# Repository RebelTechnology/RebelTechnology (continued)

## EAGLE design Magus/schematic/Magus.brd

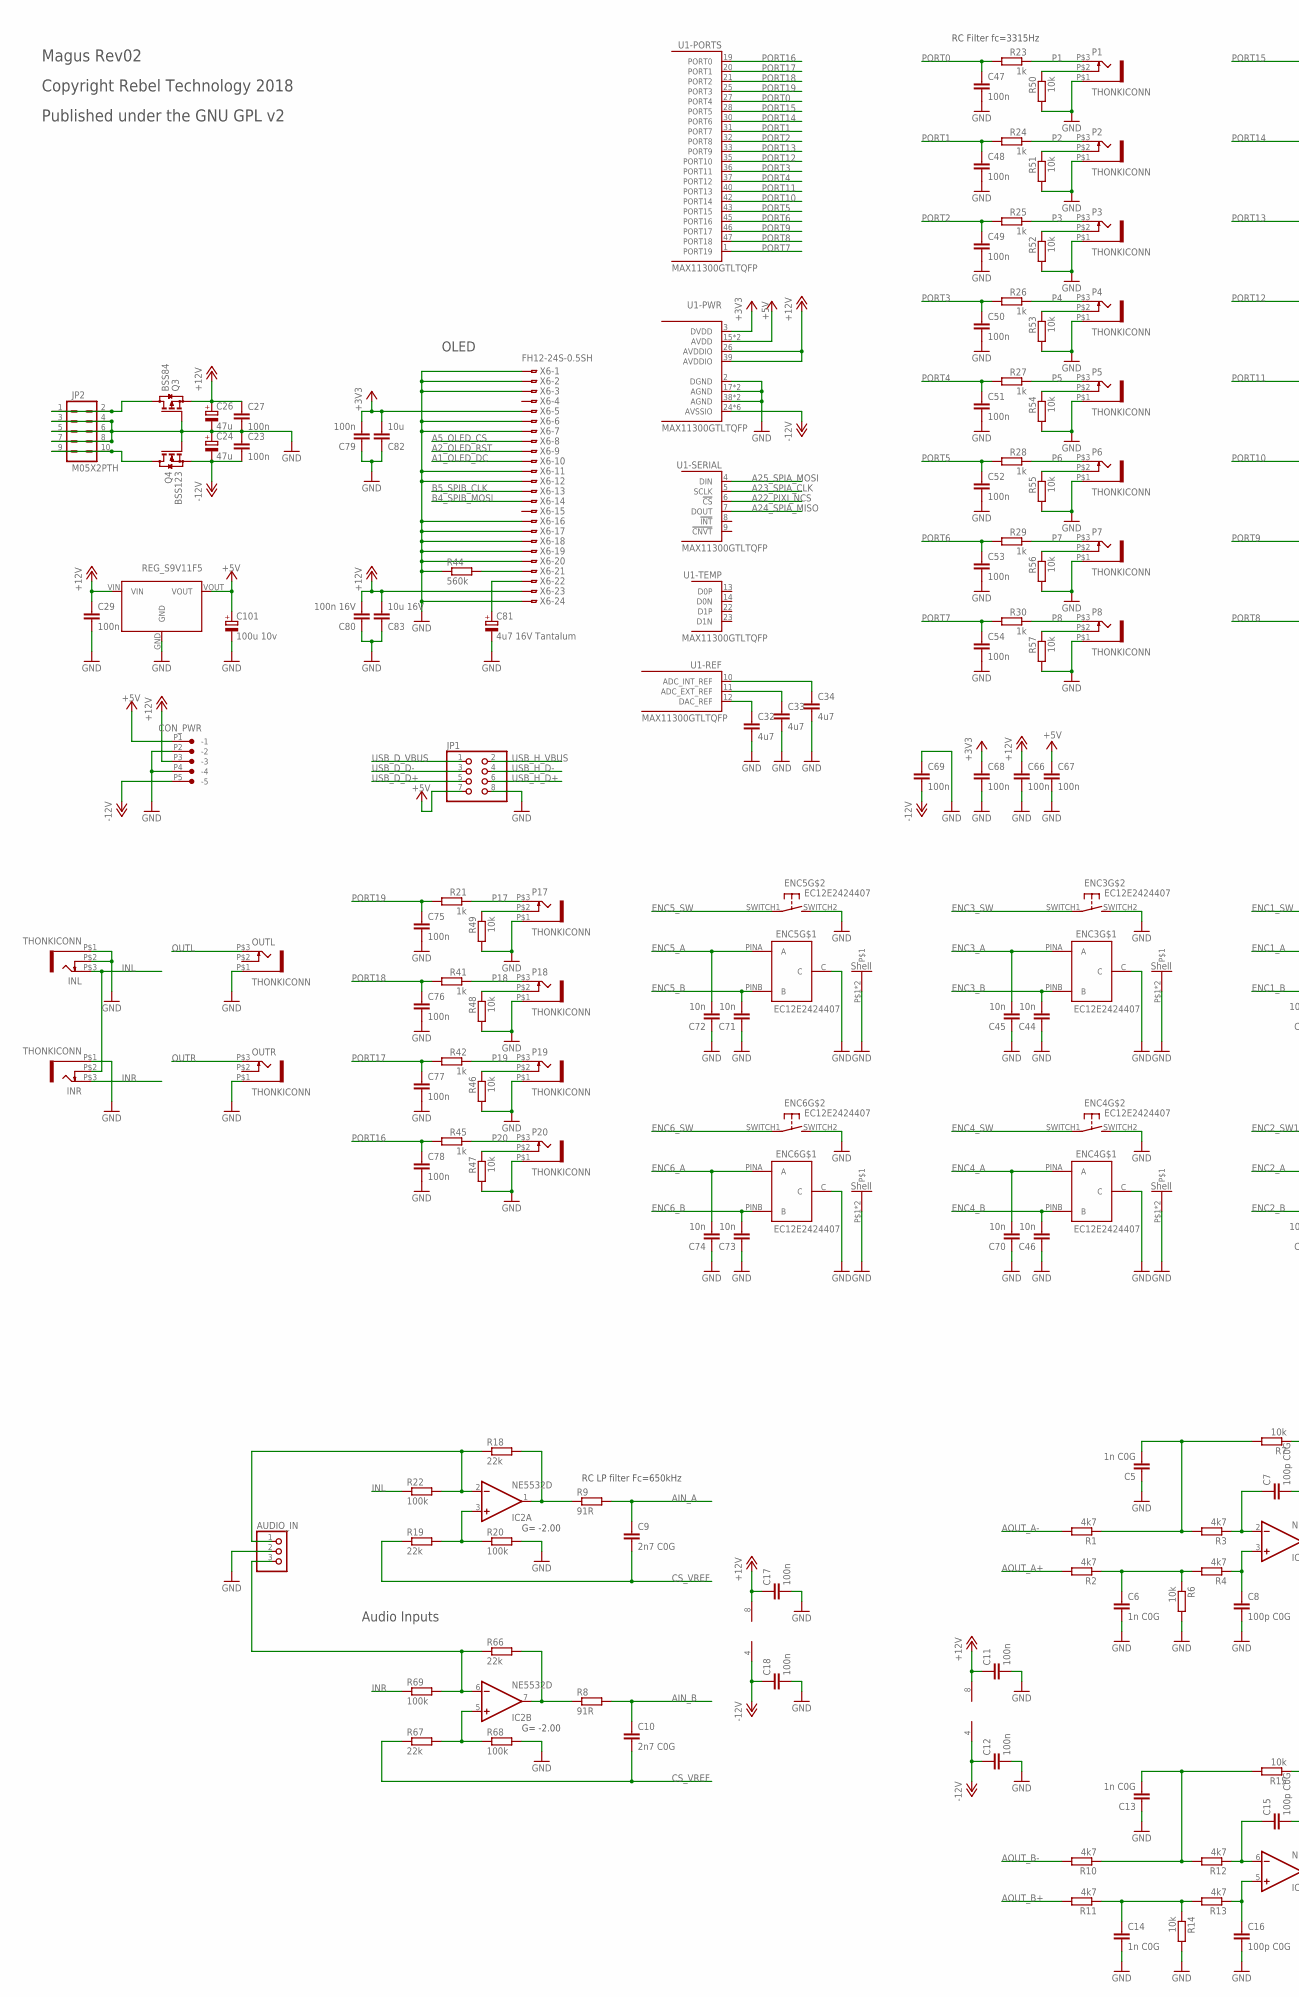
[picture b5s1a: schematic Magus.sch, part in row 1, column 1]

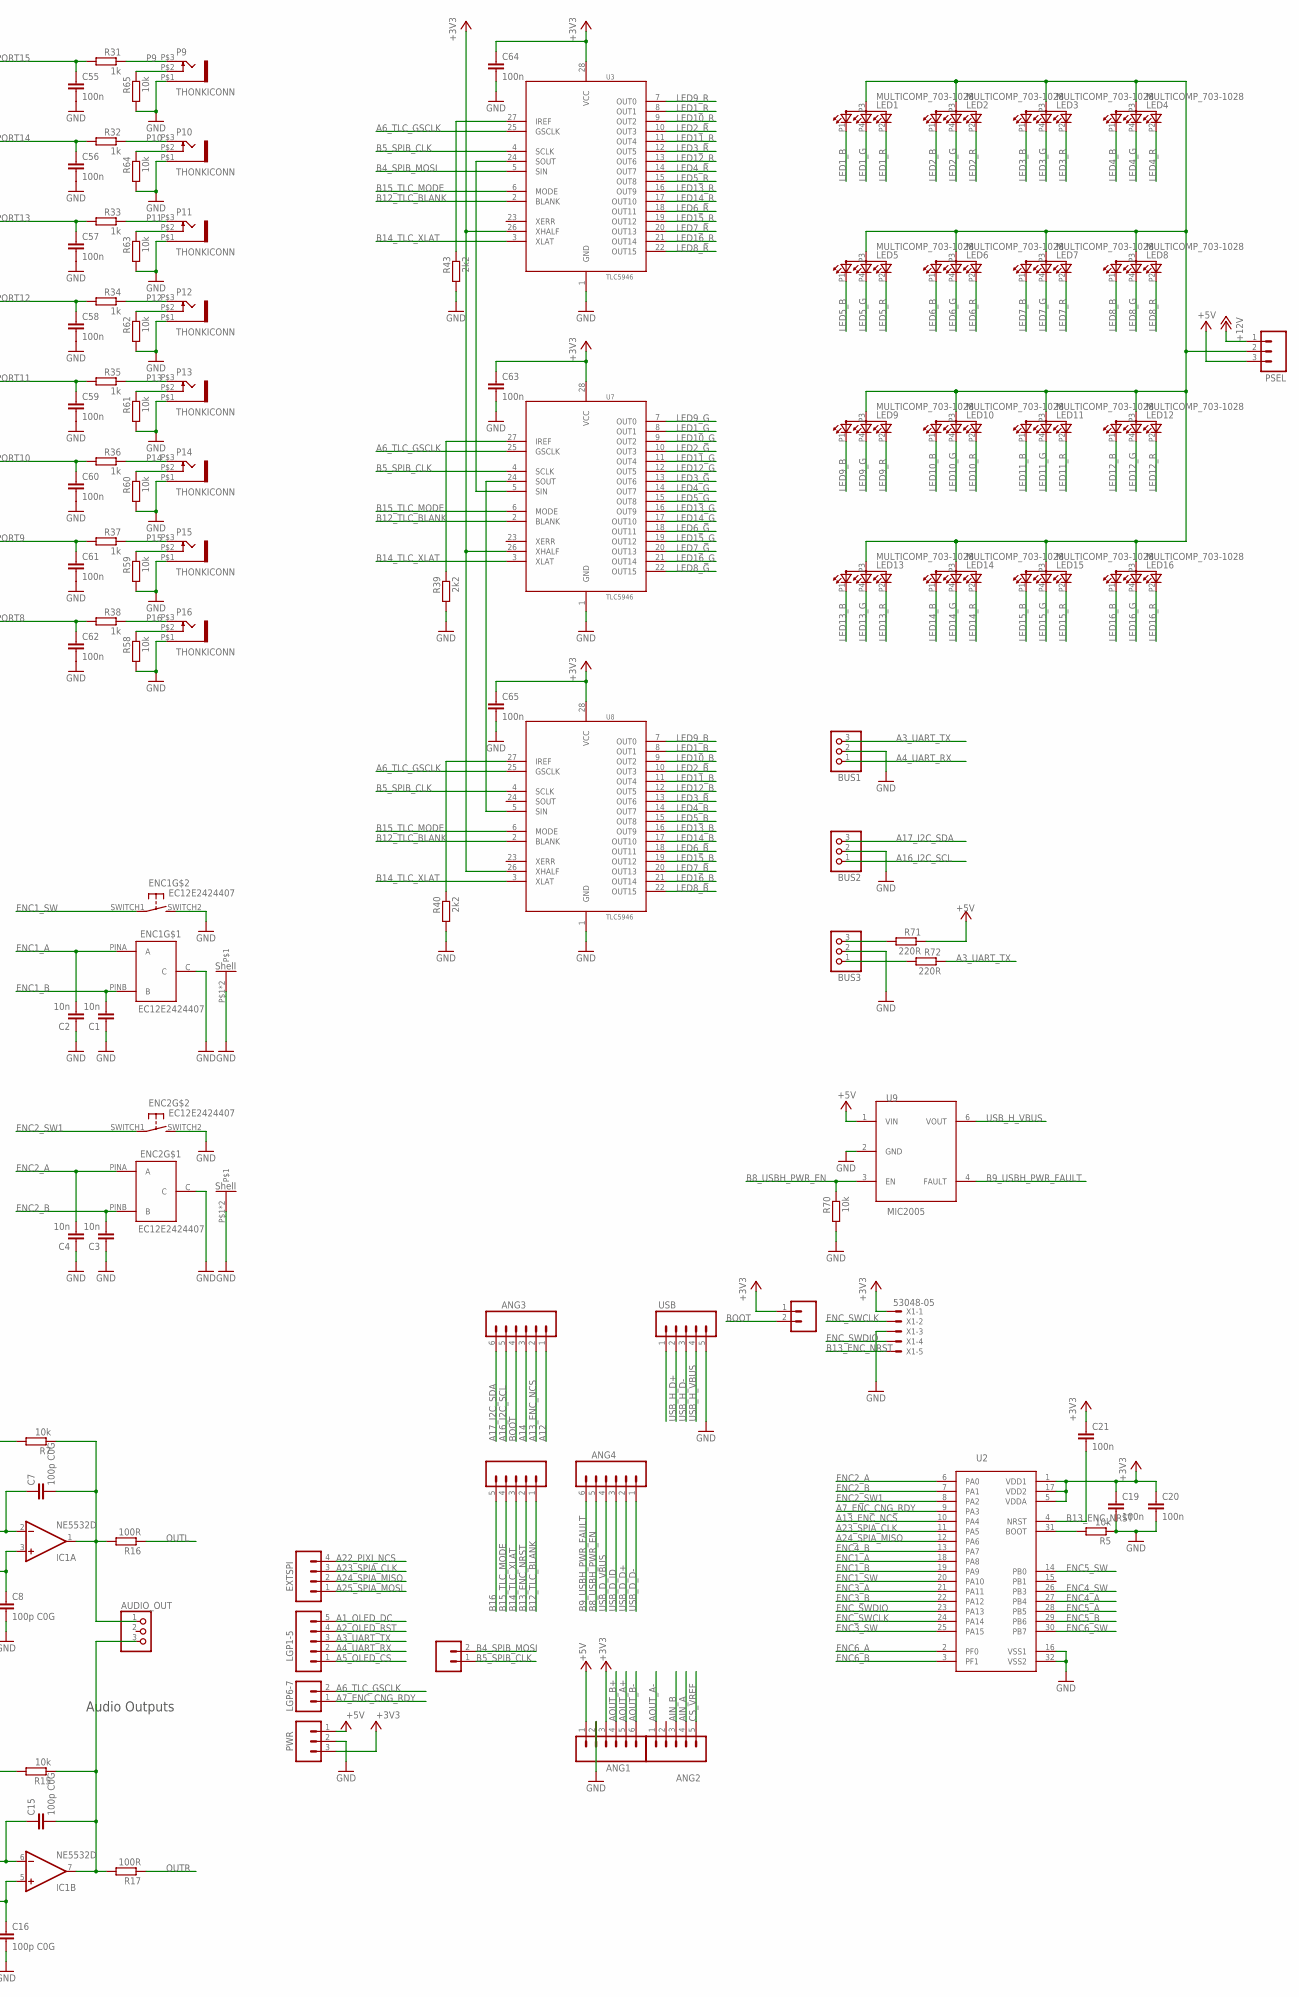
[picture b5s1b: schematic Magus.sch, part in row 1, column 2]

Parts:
ANG1, ANG3, ANG4: M06SIP; 1X06
ANG2: M05PTH; 1X05
AUDIO_IN: CON-JST-1X03PH-TH; JST-B3B-PH-KL
AUDIO_OUT: CON-JST-1X03PH-TH; JST-B3B-PH-KL
BOOT: M02PTH; 1X02
BUS1, BUS2, BUS3: CON-JST-1X03PH-TH; JST-B3B-PH-KL
C1, C2, C3, C4, C44, C45, C46, C70, C71, C72, C73, C74: 10n; C0603
C5, C6, C13, C14: 1n C0G; C0603
C7, C8, C15, C16: 100p C0G; C0603
C9, C10: 2n7 C0G; C0603
C11, C12, C17, C18, C19, C20, C21, C23, C27, C29, C47, C48, C49, C50, C51, C52, C53, C54, C55, C56, C57, C58, C59, C60, C61, C62, C63, C64, C65, C66, C67, C68, C69, C75, C76, C77, C78, C79: 100n; C0603
C24, C26: 47u; PANASONIC_B
C32, C33, C34: 4u7; C0603
C80: 100n 16V; C0603
C81: 4u7 16V Tantalum; SMC_A
C82: 10u; C1206
C83: 10u 16V; C1206
C101: 100u 10v; CPOL-5
CON_PWR: CON-JST_PH_5W
ENC1, ENC2, ENC3, ENC4, ENC5, ENC6: EC12E2424407
EXTSPI: M04PTH; 1X04
IC1, IC2: NE5532D; SO08
INL: THONKICONN
INR: THONKICONN
JP1: PINHD-2X4; 2X04
JP2: M05X2PTH; AVR_ICSP
LED1, LED2, LED3, LED4, LED5, LED6, LED7, LED8, LED9, LED10, LED11, LED12, LED13, LED14, LED15, LED16: MULTICOMP_703-1028; RGB-LED-703-1028
LGP1-5: M05PTH; 1X05
LGP6-1, LGP6-7: M02PTH; 1X02
OUTL: THONKICONN
OUTR: THONKICONN
P1, P2, P3, P4, P5, P6, P7, P8, P9, P10, P11, P12, P13, P14, P15, P16, P17, P18, P19, P20: THONKICONN
PSEL: M03PTH; 1X03
PWR: M03PTH; 1X03
Q3: BSS84; SOT23
Q4: BSS123; SOT23
R1, R2, R3, R4, R10, R11, R12, R13: 4k7; 0603
R5, R6, R7, R14, R15, R46, R47, R48, R49, R50, R51, R52, R53, R54, R55, R56, R57, R58, R59, R60, R61, R62, R63, R64, R65, R70: 10k; 0603
R8, R9: 91R; 0603
R16, R17: 100R; 0603
R18, R19, R66, R67: 22k; 0603
R20, R22, R68, R69: 100k; 0603
R21, R23, R24, R25, R26, R27, R28, R29, R30, R31, R32, R33, R34, R35, R36, R37, R38, R41, R42, R45: 1k; 0603
R39, R40, R43: 2k2; 0603
R44: 560k; 0603
R71, R72: 220R; 0603
U1: MAX11300GTLTQFP; TQFP48
U2: STM32F051K4T6; LQFP32-7X7
U3, U7, U8: TLC5946; TSSOP28
U4: REG_S9V11F5
U9: MIC2005; SOT23-6
USB, USB1: M05PTH; 1X05
X1: 53048-05
X6: FH12-24S-0.5SH

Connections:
+3V3: ANG1.3, BOOT.1, C19.1, C20.1, C21.1, C63.1, C64.1, C65.1, C68.1, C79.2, C82.2, PWR.3, U1.3 (DVDD), U2.1 (VDD1), U2.5 (VDDA), U2.17 (VDD2), U3.26 (XHALF), U3.28 (VCC), U7.26 (XHALF), U7.28 (VCC), U8.26 (XHALF), U8.28 (VCC), X1.1, X6.5
+5V: ANG1.1, C67.1, C101.+, CON_PWR.P1 (-1), JP1.7, PSEL.3, PWR.1, R71.1, U1.15 (AVDD), U1.16 (AVDD), U4.VOUT, U9.1 (VIN)
+12V: C11.1, C17.1, C26.+, C27.1, C29.1, C66.1, C80.2, C83.2, CON_PWR.P3 (-3), IC1.8 (V+), IC2.8 (V+), PSEL.1, Q3.2 (S), U1.26 (AVDDIO), U1.39 (AVDDIO), U4.VIN, X6.23
-12V: C12.1, C18.1, C23.2, C24.-, C69.2, CON_PWR.P5 (-5), IC1.4 (V-), IC2.4 (V-), Q4.2 (S), U1.24 (AVSSIO), U1.29 (AVSSIO), U1.34 (AVSSIO), U1.41 (AVSSIO), U1.44 (AVSSIO), U1.48 (AVSSIO)
A1_OLED_DC: LGP1-5.5, X6.10
A2_OLED_RST: LGP1-5.4, X6.9
A3_UART_TX: BUS1.3, LGP1-5.3, R72.1
A4_UART_RX: BUS1.1, LGP1-5.2
A5_OLED_CS: LGP1-5.1, X6.8
A6_TLC_GSCLK: LGP6-7.2, U3.25 (GSCLK), U7.25 (GSCLK), U8.25 (GSCLK)
A7_ENC_CNG_RDY: LGP6-7.1, U2.9 (PA3)
A12: ANG3.1
A13_ENC_NCS: ANG3.2, U2.10 (PA4)
A14: ANG3.3
A16_I2C_SCL: ANG3.5, BUS2.1
A17_I2C_SDA: ANG3.6, BUS2.3
A22_PIXI_NCS: EXTSPI.4, U1.6 (!CS!)
A23_SPIA_CLK: EXTSPI.3, U1.5 (SCLK), U2.11 (PA5)
A24_SPIA_MISO: EXTSPI.2, U1.7 (DOUT), U2.12 (PA6)
A25_SPIA_MOSI: EXTSPI.1, U1.4 (DIN)
AIN_A: ANG2.4, C9.1, R9.2
AIN_B: ANG2.3, C10.1, R8.2
ANALOG_OUTA1: AUDIO_OUT.1, C7.2, IC1.1 (OUT), R7.1, R16.2
ANALOG_OUTB1: AUDIO_OUT.3, C15.2, IC1.7 (OUT), R15.1, R17.2
AOUT_A+: ANG1.5, R2.2
AOUT_A-: ANG2.1, R1.2
AOUT_B+: ANG1.4, R11.2
AOUT_B-: ANG1.6, R10.2
B4_SPIB_MOSI: LGP6-1.2, U3.5 (SIN), X6.14
B5_SPIB_CLK: LGP6-1.1, U3.4 (SCLK), U7.4 (SCLK), U8.4 (SCLK), X6.13
B8_USBH_PWR_EN: ANG4.5, R70.1, U9.3 (EN)
B9_USBH_PWR_FAULT: ANG4.6, U9.4 (FAULT)
B12_TLC_BLANK: U3.2 (BLANK), U7.2 (BLANK), U8.2 (BLANK), USB1.1
B13_ENC_NRST: C21.2, U2.4 (NRST), USB1.2, X1.5
B14_TLC_XLAT: U3.3 (XLAT), U7.3 (XLAT), U8.3 (XLAT), USB1.3
B15_TLC_MODE: U3.6 (MODE), U7.6 (MODE), U8.6 (MODE), USB1.4
B16: USB1.5
BOOT: ANG3.4, BOOT.2
CS_VREF: ANG2.5, C9.2, C10.2, R19.1, R67.1
ENC1_A: C2.2, ENC1.PINA (A), U2.18 (PA8)
ENC1_B: C1.2, ENC1.PINB (B), U2.19 (PA9)
ENC1_SW: ENC1.SWITCH1, U2.20 (PA10)
ENC2_A: C4.2, ENC2.PINA (A), U2.6 (PA0)
ENC2_B: C3.2, ENC2.PINB (B), U2.7 (PA1)
ENC2_SW: ENC2.SWITCH1, U2.8 (PA2)
ENC3_A: C45.2, ENC3.PINA (A), U2.21 (PA11)
ENC3_B: C44.2, ENC3.PINB (B), U2.22 (PA12)
ENC3_SW: ENC3.SWITCH1, U2.25 (PA15)
ENC4_A: C70.2, ENC4.PINA (A), U2.27 (PB4)
ENC4_B: C46.2, ENC4.PINB (B), U2.13 (PA7)
ENC4_SW: ENC4.SWITCH1, U2.26 (PB3)
ENC5_A: C72.2, ENC5.PINA (A), U2.28 (PB5)
ENC5_B: C71.2, ENC5.PINB (B), U2.29 (PB6)
ENC5_SW: ENC5.SWITCH1, U2.14 (PB0)
ENC6_A: C74.2, ENC6.PINA (A), U2.2 (PF0)
ENC6_B: C73.2, ENC6.PINB (B), U2.3 (PF1)
ENC6_SW: ENC6.SWITCH1, U2.30 (PB7)
ENC_SWCLK: U2.24 (PA14), X1.2
ENC_SWDIO: U2.23 (PA13), X1.4
GND: ANG1.2, AUDIO_IN.2, BUS1.2, BUS2.2, BUS3.2, C1.1, C2.1, C3.1, C4.1, C5.1, C6.2, C8.2, C11.2, C12.2, C13.1, C14.2, C16.2, C17.2, C18.2, C19.2, C20.2, C23.1, C24.+, C26.-, C27.2, C29.2, C32.2, C33.2, C34.2, C44.1, C45.1, C46.1, C47.2, C48.2, C49.2, C50.2, C51.2, C52.2, C53.2, C54.2, C55.2, C56.2, C57.2, C58.2, C59.2, C60.2, C61.2, C62.2, C63.2, C64.2, C65.2, C66.2, C67.2, C68.2, C69.1, C70.1, C71.1, C72.1, C73.1, C74.1, C75.2, C76.2, C77.2, C78.2, C79.1, C80.1, C81.-, C82.1, C83.1, C101.-, CON_PWR.P2 (-2), CON_PWR.P4 (-4), ENC1.C, ENC1.P$1, ENC1.P$2, ENC1.SWITCH2 (S), ENC2.C, ENC2.P$1, ENC2.P$2, ENC2.SWITCH2 (S), ENC3.C, ENC3.P$1, ENC3.P$2, ENC3.SWITCH2 (S), ENC4.C, ENC4.P$1, ENC4.P$2, ENC4.SWITCH2 (S), ENC5.C, ENC5.P$1, ENC5.P$2, ENC5.SWITCH2 (S), ENC6.C, ENC6.P$1, ENC6.P$2, ENC6.SWITCH2 (S), INL.P$1 (5), INL.P$2 (4), INR.P$1 (5), JP1.8, JP2.3, JP2.4, JP2.5, JP2.7, JP2.8, OUTL.P$1 (5), OUTR.P$1 (5), P1.P$1 (5), P2.P$1 (5), P3.P$1 (5), P4.P$1 (5), P5.P$1 (5), P6.P$1 (5), P7.P$1 (5), P8.P$1 (5), P9.P$1 (5), P10.P$1 (5), P11.P$1 (5), P12.P$1 (5), P13.P$1 (5), P14.P$1 (5), P15.P$1 (5), P16.P$1 (5), P17.P$1 (5), P18.P$1 (5), P19.P$1 (5), P20.P$1 (5), PWR.2, Q3.1 (G), Q4.1 (G), R5.1, R6.2, R14.2, R20.2, R39.2, R40.2, R43.2, R44.1, R46.2, R47.2, R48.2, R49.2, R50.2, R51.2, R52.2, R53.2, R54.2, R55.2, R56.2, R57.2, R58.2, R59.2, R60.2, R61.2, R62.2, R63.2, R64.2, R65.2, R68.2, R70.2, U1.2 (DGND), U1.17 (AGND), U1.18 (AGND), U1.38 (AGND), U1.EP (AGND), U2.16 (VSS1), U2.32 (VSS2), U3.1 (GND), U4.GND, U7.1 (GND), U8.1 (GND), U9.2 (GND), USB.5, X1.3, X6.1, X6.2, X6.3, X6.6, X6.7, X6.11, X6.12, X6.16, X6.17, X6.18, X6.19, X6.20, X6.24
INL: INL.P$3 (3), INR.P$2 (4), R22.1
INR: INR.P$3 (3), R69.1
LED1_B: LED1.P1 (CRED), U8.8 (OUT1)
LED1_G: LED1.P4 (CBLUE), U7.8 (OUT1)
LED1_R: LED1.P2 (CGREEN), U3.8 (OUT1)
LED2_B: LED2.P1 (CRED), U8.10 (OUT3)
LED2_G: LED2.P4 (CBLUE), U7.10 (OUT3)
LED2_R: LED2.P2 (CGREEN), U3.10 (OUT3)
LED3_B: LED3.P1 (CRED), U8.13 (OUT6)
LED3_G: LED3.P4 (CBLUE), U7.13 (OUT6)
LED3_R: LED3.P2 (CGREEN), U3.12 (OUT5)
LED4_B: LED4.P1 (CRED), U8.14 (OUT7)
LED4_G: LED4.P4 (CBLUE), U7.14 (OUT7)
LED4_R: LED4.P2 (CGREEN), U3.14 (OUT7)
LED5_B: LED5.P1 (CRED), U8.15 (OUT8)
LED5_G: LED5.P4 (CBLUE), U7.15 (OUT8)
LED5_R: LED5.P2 (CGREEN), U3.15 (OUT8)
LED6_B: LED6.P1 (CRED), U8.18 (OUT11)
LED6_G: LED6.P4 (CBLUE), U7.18 (OUT11)
LED6_R: LED6.P2 (CGREEN), U3.18 (OUT11)
LED7_B: LED7.P1 (CRED), U8.20 (OUT13)
LED7_G: LED7.P4 (CBLUE), U7.20 (OUT13)
LED7_R: LED7.P2 (CGREEN), U3.20 (OUT13)
LED8_B: LED8.P1 (CRED), U8.22 (OUT15)
LED8_G: LED8.P4 (CBLUE), U7.22 (OUT15)
LED8_R: LED8.P2 (CGREEN), U3.22 (OUT15)
LED9_B: LED9.P1 (CRED), U8.7 (OUT0)
LED9_G: LED9.P4 (CBLUE), U7.7 (OUT0)
LED9_R: LED9.P2 (CGREEN), U3.7 (OUT0)
LED10_B: LED10.P1 (CRED), U8.9 (OUT2)
LED10_G: LED10.P4 (CBLUE), U7.9 (OUT2)
LED10_R: LED10.P2 (CGREEN), U3.9 (OUT2)
LED11_B: LED11.P1 (CRED), U8.11 (OUT4)
LED11_G: LED11.P4 (CBLUE), U7.11 (OUT4)
LED11_R: LED11.P2 (CGREEN), U3.11 (OUT4)
LED12_B: LED12.P1 (CRED), U8.12 (OUT5)
LED12_G: LED12.P4 (CBLUE), U7.12 (OUT5)
LED12_R: LED12.P2 (CGREEN), U3.13 (OUT6)
LED13_B: LED13.P1 (CRED), U8.16 (OUT9)
LED13_G: LED13.P4 (CBLUE), U7.16 (OUT9)
LED13_R: LED13.P2 (CGREEN), U3.16 (OUT9)
LED14_B: LED14.P1 (CRED), U8.17 (OUT10)
LED14_G: LED14.P4 (CBLUE), U7.17 (OUT10)
LED14_R: LED14.P2 (CGREEN), U3.17 (OUT10)
LED15_B: LED15.P1 (CRED), U8.19 (OUT12)
LED15_G: LED15.P4 (CBLUE), U7.19 (OUT12)
LED15_R: LED15.P2 (CGREEN), U3.19 (OUT12)
LED16_B: LED16.P1 (CRED), U8.21 (OUT14)
LED16_G: LED16.P4 (CBLUE), U7.21 (OUT14)
LED16_R: LED16.P2 (CGREEN), U3.21 (OUT14)
LED_PWR: LED1.P3 (A), LED2.P3 (A), LED3.P3 (A), LED4.P3 (A), LED5.P3 (A), LED6.P3 (A), LED7.P3 (A), LED8.P3 (A), LED9.P3 (A), LED10.P3 (A), LED11.P3 (A), LED12.P3 (A), LED13.P3 (A), LED14.P3 (A), LED15.P3 (A), LED16.P3 (A), PSEL.2
unnamed: C34.1, U1.10 (ADC_INT_REF)
unnamed: IC2.3 (+IN), R19.2, R20.1
unnamed: AUDIO_IN.1, IC2.2 (-IN), R18.1, R22.2
unnamed: IC2.1 (OUT), R9.1, R18.2
unnamed: IC2.5 (+IN), R67.2, R68.1
unnamed: AUDIO_IN.3, IC2.6 (-IN), R66.1, R69.2
unnamed: C33.1, U1.11 (ADC_EXT_REF)
unnamed: IC2.7 (OUT), R8.1, R66.2
unnamed: C32.1, U1.12 (DAC_REF)
unnamed: JP2.9, JP2.10, Q4.3 (D)
unnamed: C6.1, R2.1, R4.2, R6.1
unnamed: C5.2, R1.1, R3.2, R7.2
unnamed: JP2.1, JP2.2, Q3.3 (D)
unnamed: BUS3.3, R71.2
unnamed: C7.1, IC1.2 (-IN), R3.1
unnamed: C8.1, IC1.3 (+IN), R4.1
unnamed: C14.1, R11.1, R13.2, R14.1
unnamed: C13.2, R10.1, R12.2, R15.2
unnamed: C15.1, IC1.6 (-IN), R12.1
unnamed: C16.1, IC1.5 (+IN), R13.1
unnamed: BUS3.1, R72.2
unnamed: R5.2, U2.31 (BOOT)
unnamed: U3.24 (SOUT), U7.5 (SIN)
unnamed: R39.1, U7.27 (IREF)
unnamed: R40.1, U8.27 (IREF)
unnamed: U7.24 (SOUT), U8.5 (SIN)
unnamed: P9.P$2 (4), R65.1
unnamed: P10.P$2 (4), R64.1
unnamed: R43.1, U3.27 (IREF)
unnamed: P11.P$2 (4), R63.1
unnamed: P12.P$2 (4), R62.1
unnamed: P13.P$2 (4), R61.1
unnamed: P14.P$2 (4), R60.1
unnamed: P15.P$2 (4), R59.1
unnamed: P16.P$2 (4), R58.1
unnamed: P8.P$2 (4), R57.1
unnamed: P7.P$2 (4), R56.1
unnamed: P6.P$2 (4), R55.1
unnamed: P5.P$2 (4), R54.1
unnamed: P4.P$2 (4), R53.1
unnamed: P3.P$2 (4), R52.1
unnamed: P2.P$2 (4), R51.1
unnamed: P1.P$2 (4), R50.1
unnamed: P17.P$2 (4), R49.1
unnamed: P18.P$2 (4), R48.1
unnamed: P19.P$2 (4), R46.1
unnamed: P20.P$2 (4), R47.1
unnamed: C81.+, X6.22
unnamed: R44.2, X6.21
OUTL: OUTL.P$3 (3), R16.1
OUTR: OUTR.P$3 (3), R17.1
P1: P1.P$3 (3), R23.1
P2: P2.P$3 (3), R24.1
P3: P3.P$3 (3), R25.1
P4: P4.P$3 (3), R26.1
P5: P5.P$3 (3), R27.1
P6: P6.P$3 (3), R28.1
P7: P7.P$3 (3), R29.1
P8: P8.P$3 (3), R30.1
P9: P9.P$3 (3), R31.1
P10: P10.P$3 (3), R32.1
P11: P11.P$3 (3), R33.1
P12: P12.P$3 (3), R34.1
P13: P13.P$3 (3), R35.1
P14: P14.P$3 (3), R36.1
P15: P15.P$3 (3), R37.1
P16: P16.P$3 (3), R38.1
P17: P17.P$3 (3), R21.1
P18: P18.P$3 (3), R41.1
P19: P19.P$3 (3), R42.1
P20: P20.P$3 (3), R45.1
PORT0: C47.1, R23.2, U1.27 (PORT4)
PORT1: C48.1, R24.2, U1.31 (PORT7)
PORT2: C49.1, R25.2, U1.32 (PORT8)
PORT3: C50.1, R26.2, U1.36 (PORT11)
PORT4: C51.1, R27.2, U1.37 (PORT12)
PORT5: C52.1, R28.2, U1.43 (PORT15)
PORT6: C53.1, R29.2, U1.45 (PORT16)
PORT7: C54.1, R30.2, U1.1 (PORT19)
PORT8: C62.1, R38.2, U1.47 (PORT18)
PORT9: C61.1, R37.2, U1.46 (PORT17)
PORT10: C60.1, R36.2, U1.42 (PORT14)
PORT11: C59.1, R35.2, U1.40 (PORT13)
PORT12: C58.1, R34.2, U1.35 (PORT10)
PORT13: C57.1, R33.2, U1.33 (PORT9)
PORT14: C56.1, R32.2, U1.30 (PORT6)
PORT15: C55.1, R31.2, U1.28 (PORT5)
PORT16: C78.1, R45.2, U1.19 (PORT0)
PORT17: C77.1, R42.2, U1.20 (PORT1)
PORT18: C76.1, R41.2, U1.21 (PORT2)
PORT19: C75.1, R21.2, U1.25 (PORT3)
USB_D_D+: ANG4.2, JP1.5
USB_D_D-: ANG4.1, JP1.3
USB_D_VBUS: ANG4.4, JP1.1
USB_H_D+: JP1.6, USB.2
USB_H_D-: JP1.4, USB.3
USB_H_VBUS: JP1.2, U9.6 (VOUT), USB.4

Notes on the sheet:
RC Filter fc=3315Hz
Magus Rev02
Copyright Rebel Technology 2018
OLED
RC LP filter Fc=650kHz
Audio Outputs
Audio Inputs
G= -2.00
Published under the GNU GPL v2

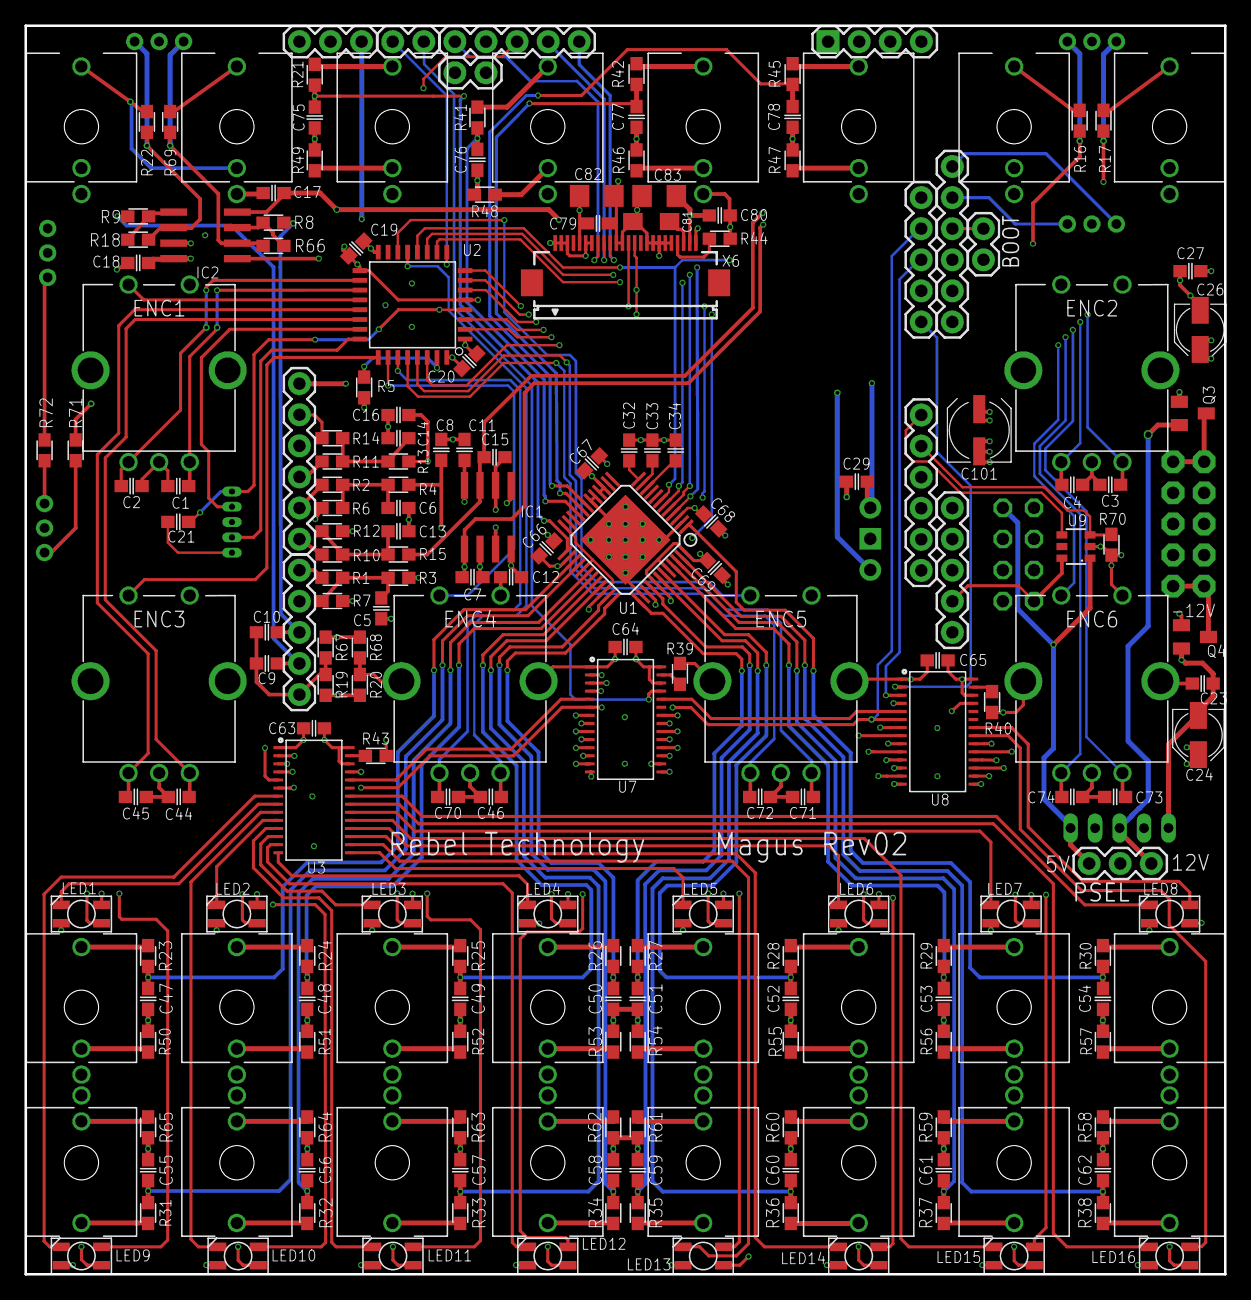
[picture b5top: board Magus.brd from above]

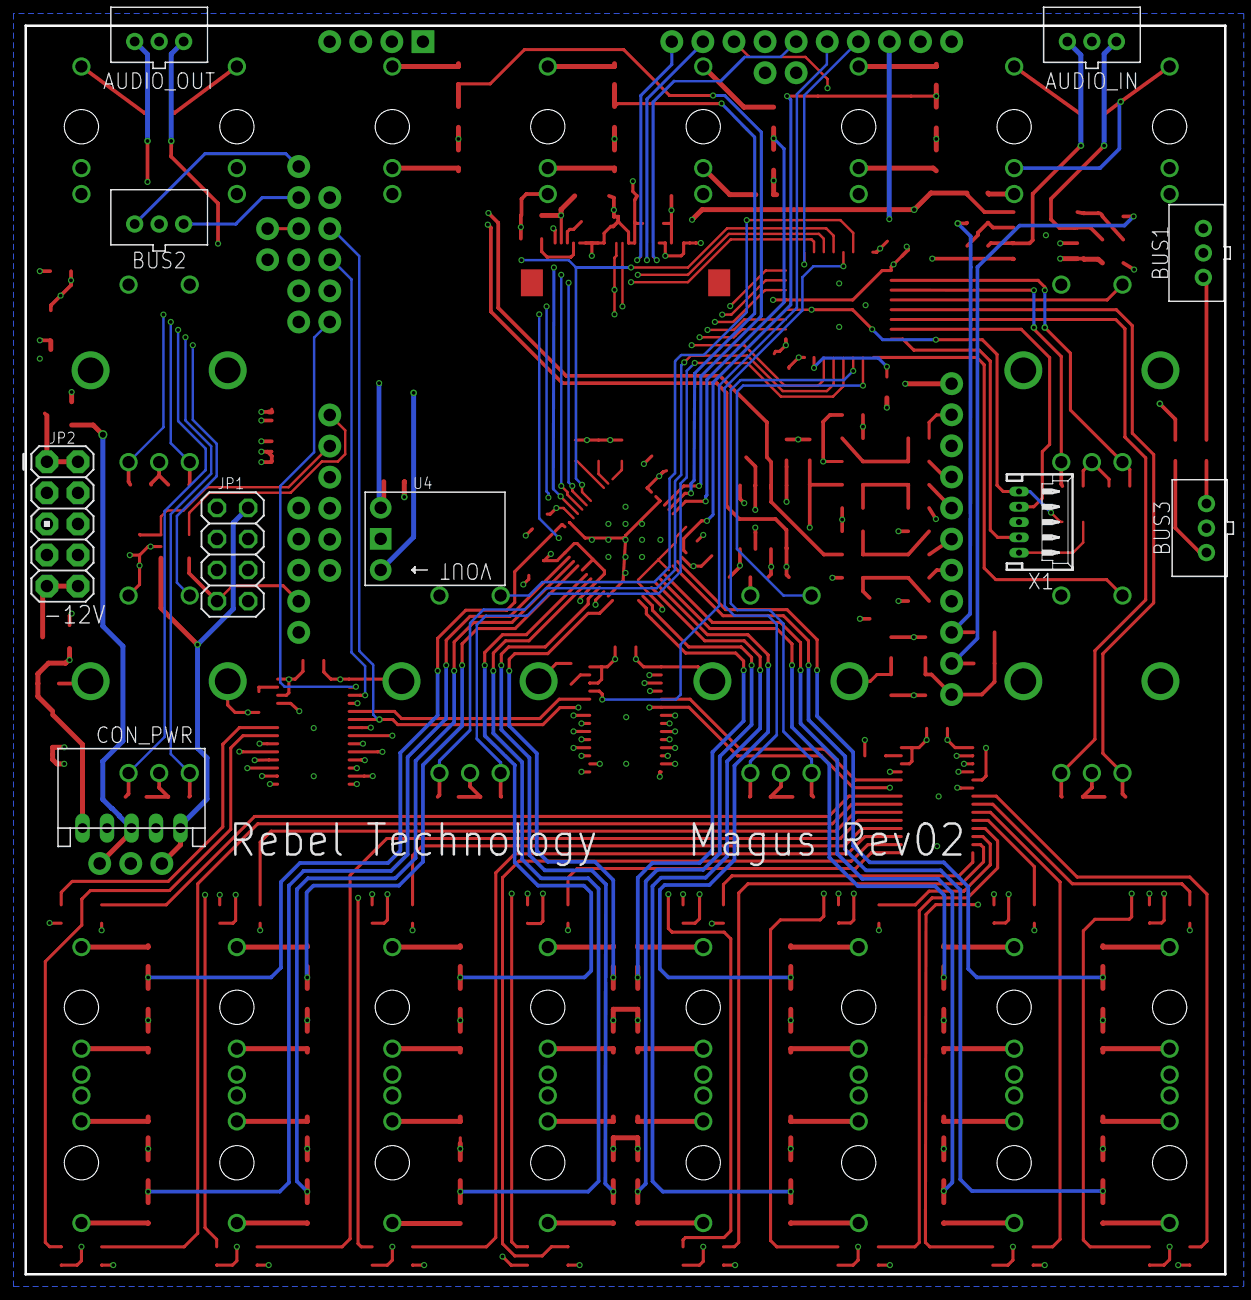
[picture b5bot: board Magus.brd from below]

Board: 4 copper layers, 98.0 x 102.0 mm, 222 parts (10 on the bottom side), 205 nets.

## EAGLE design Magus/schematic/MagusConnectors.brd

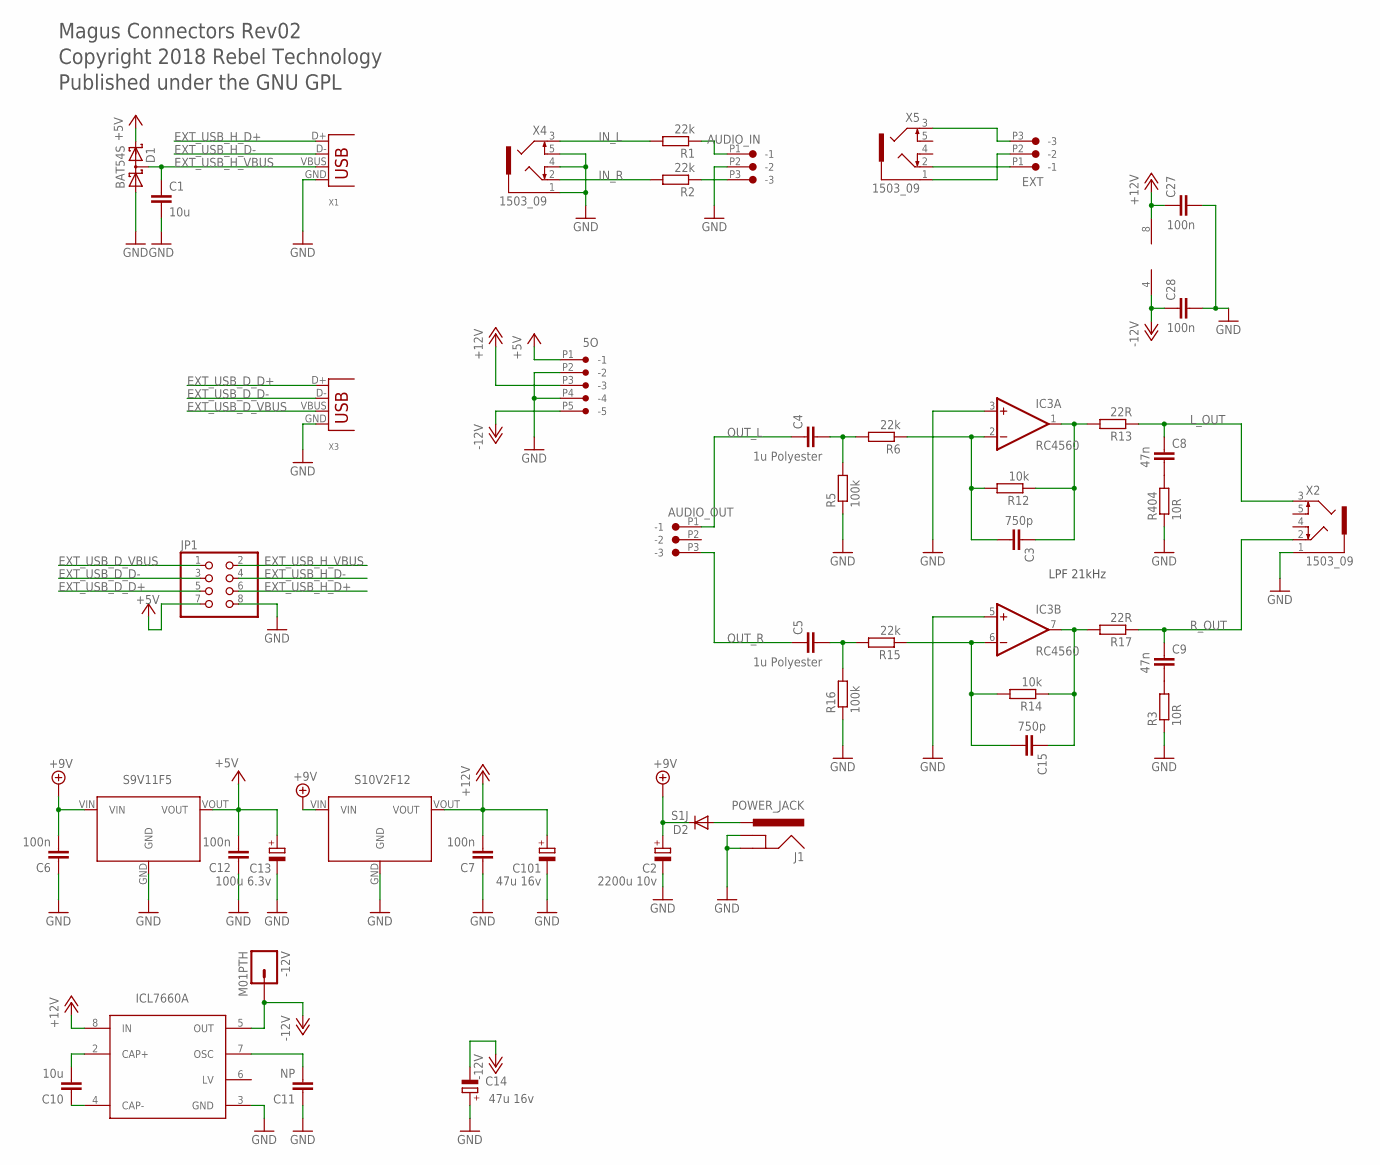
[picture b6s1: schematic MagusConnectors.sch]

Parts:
5O: CON-JST_PH_5W
-12V: M01PTH; 1X01
AUDIO_IN: CON-JST_PH_3W
AUDIO_OUT: CON-JST_PH_3W
C1, C10: 10u; C1206
C2: 2200u 10v; PANASONIC_D
C3, C15: 750p; C0603
C4, C5: 1u Polyester; C1210
C6, C7, C12, C27, C28: 100n; C0603
C8, C9: 47n; C0603
C11: NP; C0603
C13: 100u 6.3v; PANASONIC_B
C14, C101: 47u 16v; PANASONIC_B
D1: BAT54S; SOT23
D2: S1J; SMA-DIODE
EXT: CON-JST_PH_3W
IC3: RC4560; SO08
J1: POWER_JACK; DC_JACK_SLOT
JP1: PINHD-2X4; 2X04
R1, R2, R6, R15: 22k; R0603
R3, R404: 10R; R0603
R5, R16: 100k; R0603
R12, R14: 10k; R0603
R13, R17: 22R; R0603
U1: S9V11F5; REG_S9V11F5
U2: S10V2F12; REG_S9V11F5
U3: ICL7660A; SOIC8
X1: USB-A-H
X2, X4, X5: 1503_09
X3: USB-B-H

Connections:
+5V: 5O.P1 (-1), C12.2, C13.+, D1.2 (C2), JP1.7, U1.VOUT
+9V: C2.+, C6.2, D2.C, U1.VIN, U2.VIN
+12V: 5O.P3 (-3), C7.2, C27.1, C101.+, IC3.8 (V+), U2.VOUT, U3.8 (IN)
-12V: 5O.P5 (-5), -12V.1, C14.-, C28.1, IC3.4 (V-), U3.5 (OUT)
EXT_USB_D_D+: JP1.5, X3.D+
EXT_USB_D_D-: JP1.3, X3.D-
EXT_USB_D_VBUS: JP1.1, X3.VBUS
EXT_USB_H_D+: JP1.6, X1.D+
EXT_USB_H_D-: JP1.4, X1.D-
EXT_USB_H_VBUS: C1.1, D1.3 (C1A2), JP1.2, X1.VBUS
GND: 5O.P2 (-2), 5O.P4 (-4), AUDIO_IN.P2 (-2), C1.2, C2.-, C6.1, C7.1, C11.1, C12.1, C13.-, C14.+, C27.2, C28.2, C101.-, D1.1 (A1), IC3.3 (+IN), IC3.5 (+IN), J1.GND, J1.GNDBREAK, JP1.8, R3.1, R5.1, R16.1, R404.1, U1.GND, U2.GND, U3.3 (GND), X1.GND, X2.1, X3.GND, X4.1, X4.4, X4.5
IN_L: R1.2, X4.3
IN_R: R2.2, X4.2
L_OUT: C8.1, R13.1, X2.3
unnamed: C15.2, IC3.6 (-IN), R14.2, R15.1
unnamed: C15.1, IC3.7 (OUT), R14.1, R17.2
unnamed: C3.2, IC3.2 (-IN), R6.1, R12.2
unnamed: C5.2, R15.2, R16.2
unnamed: AUDIO_IN.P3 (-3), R2.1
unnamed: AUDIO_IN.P1 (-1), R1.1
unnamed: EXT.P1 (-1), X5.2
unnamed: C4.2, R5.2, R6.2
unnamed: D2.A, J1.PWR
unnamed: C10.1, U3.4 (CAP-)
unnamed: C10.2, U3.2 (CAP+)
unnamed: C9.2, R3.2
unnamed: C11.2, U3.7 (OSC)
unnamed: EXT.P3 (-3), X5.3
unnamed: EXT.P2 (-2), X5.1
unnamed: C3.1, IC3.1 (OUT), R12.1, R13.2
unnamed: C8.2, R404.2
OUT_L: AUDIO_OUT.P1 (-1), C4.1
OUT_R: AUDIO_OUT.P3 (-3), C5.1
R_OUT: C9.1, R17.1, X2.2

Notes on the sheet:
Magus Connectors Rev02
Copyright 2018 Rebel Technology
Published under the GNU GPL
LPF 21kHz

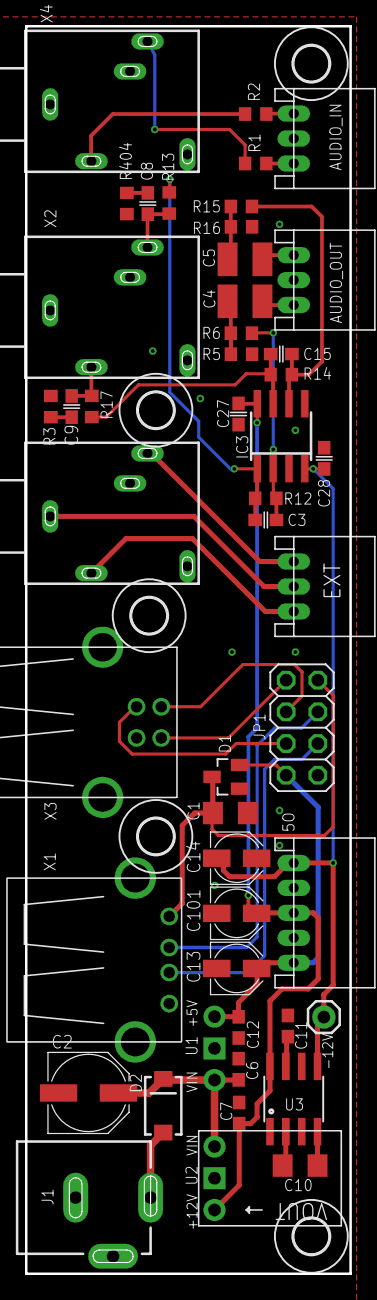
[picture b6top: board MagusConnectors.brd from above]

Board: 2 copper layers, 26.0 x 100.0 mm, 53 parts (1 on the bottom side), 34 nets.

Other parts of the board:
U$1, U$2, U$3, U$4, U$5: 2,8
